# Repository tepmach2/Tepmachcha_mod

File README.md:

# Tepmachcha_mod

Reworking of original Tepmachcha board for improved stability and mechanical access to seeed stalker board below.

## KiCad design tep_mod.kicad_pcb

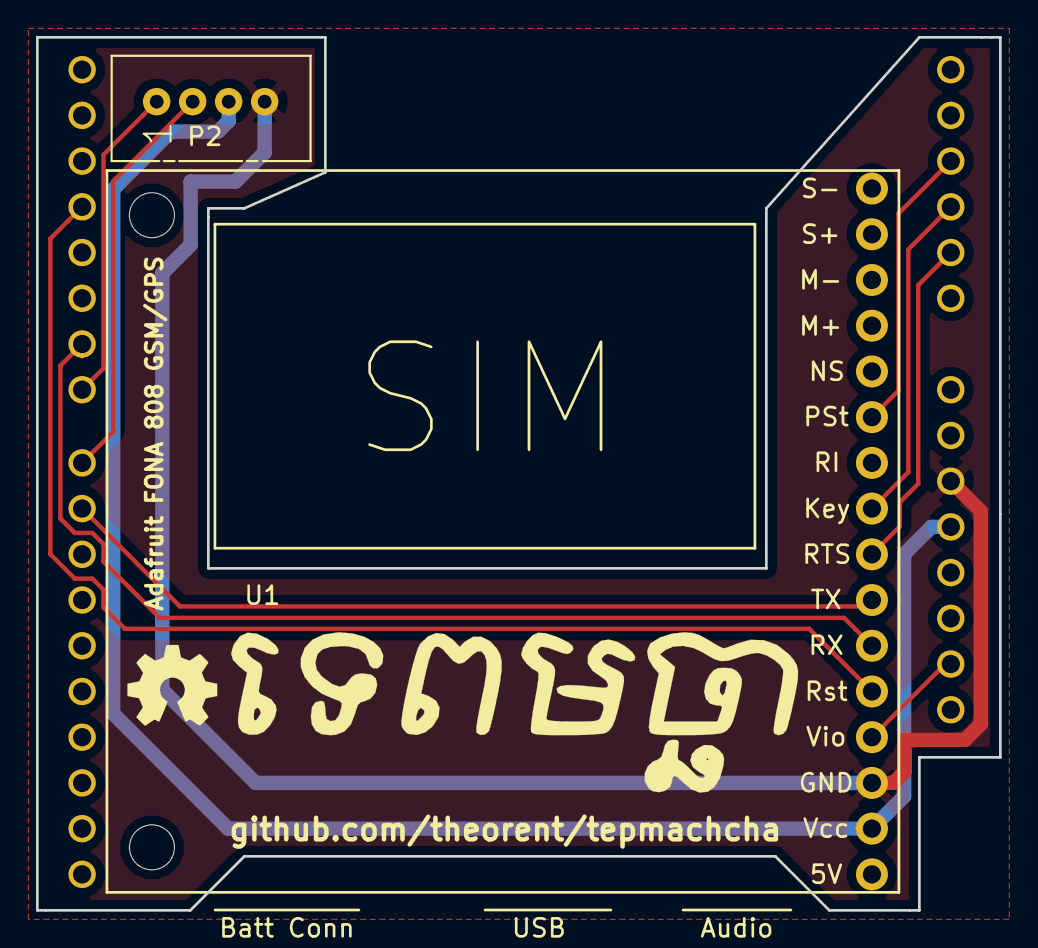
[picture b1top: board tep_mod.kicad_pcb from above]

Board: 2 copper layers, 53.5 x 48.5 mm, 4 parts (0 on the bottom side), 11 nets.

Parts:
LOGO_OSHW_silkscreen_5mm: val**; LOGO_OSHW_silkscreen_5mm
P2: CONN_01X04; Grove_1x04
SHIELD1: ARDUINO_SHIELD
U1: FONA_808; Adafruit_FONA_808_Theorent

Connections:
GND: P2.4, SHIELD1.GND1, U1.3
unnamed: P2.1, SHIELD1.7
unnamed: P2.2, SHIELD1.8
unnamed: SHIELD1.3, U1.5
unnamed: SHIELD1.6, U1.6
unnamed: SHIELD1.9, U1.7
unnamed: SHIELD1.AD1, U1.8
unnamed: SHIELD1.AD2, U1.9
unnamed: SHIELD1.AD3, U1.11
unnamed: SHIELD1.IO_R, U1.4
VCC: P2.3, SHIELD1.5V, U1.2

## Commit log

2017-04-07 Initial commit
    Cicada project elements copied over
2017-04-07 Pin assignment changes
    Freeing SPI bus for SD card use. Adding ICSP breakout on top. RTS pin
    assigned. Other small changes and tidying up.
2017-04-10 v 0.1 board files
2017-04-27 Add logos in new graphics library
2017-04-28 Added Khmer script
    Added Tepmachcha to board in Khmer OS script. Output directory change
    (but it’s still local sorry)
2017-05-21 Pictures of finished boards
